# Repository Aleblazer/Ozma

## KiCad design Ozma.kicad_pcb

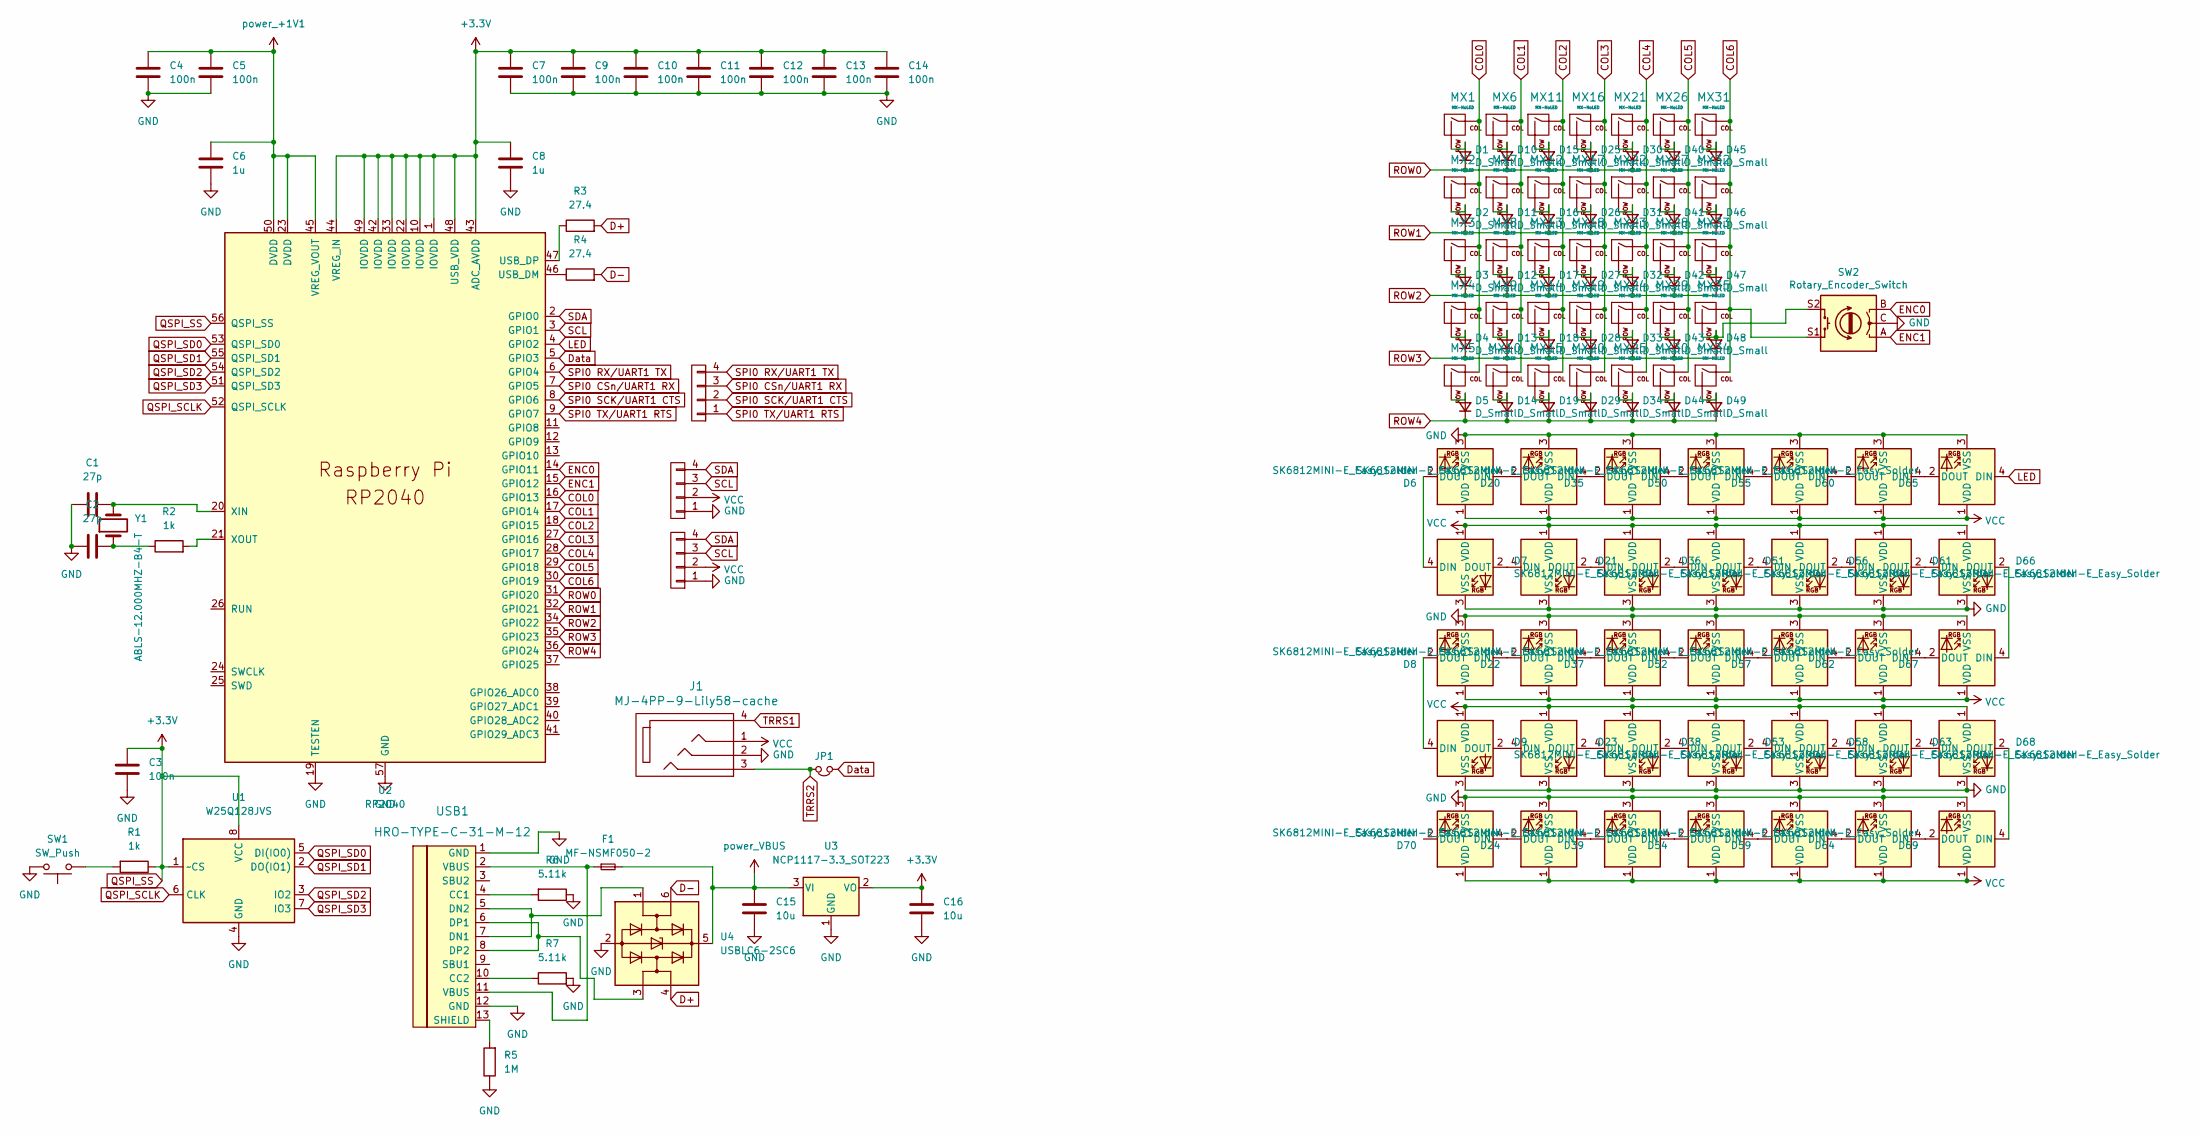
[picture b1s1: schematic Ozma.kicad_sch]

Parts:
C1, C2: 27p; R_0402_1005Metric; LCSC C1557
C3, C4, C5, C7, C9, C10, C11, C12, C13, C14: 100n; R_0402_1005Metric; LCSC C60474
C6, C8: 1u; R_0402_1005Metric; LCSC C314234
C15, C16: 10u; R_1206_3216Metric; LCSC C92790
D1, D2, D3, D4, D5, D10, D11, D12, D13, D14, D15, D16, D17, D18, D19, D25, D26, D27, D28, D29, D30, D31, D32, D33, D34, D40, D41, D42, D43, D44, D45, D46, D47, D48, D49: D_Small; D_SOD-123F; LCSC C132821
D6, D7, D8, D9, D20, D21, D22, D23, D24, D35, D36, D37, D38, D39, D50, D51, D52, D53, D54, D55, D56, D57, D58, D59, D60, D61, D62, D63, D64, D65, D66, D67, D68, D69, D70: SK6812MINI-E_Easy_Solder; YS-SK6812MINI-E
F1: MF-NSMF050-2; Fuse_1206_3216Metric; LCSC C75464
J1: MJ-4PP-9-Lily58-cache; MJ-4PP-9_rev2; LCSC C95562
JP1: Jumper_NC_Small; jumper_data
MX1, MX2, MX3, MX4, MX5, MX6, MX7, MX8, MX9, MX10, MX11, MX12, MX13, MX14, MX15, MX16, MX17, MX18, MX19, MX20, MX21, MX22, MX23, MX24, MX25, MX26, MX27, MX28, MX29, MX30, MX31, MX32, MX34, MX35: MX-NoLED; MX-Alps-Choc-1U-NoLED
MX33: MX-NoLED; MX-Alps-Choc-2u-StabFlip-NoLED
P1, P2, P3: OLED; OLED_4Pin
R1, R2: 1k; R_0402_1005Metric; LCSC C491161
R3, R4: 27.4; R_0402_1005Metric; LCSC C172043
R5: 1M; R_0402_1005Metric; LCSC C144054
R6, R7: 5.11k; R_0402_1005Metric; LCSC C25906
SW1: SW_Push; TACT_SWITCH_TVBP06
SW2: Rotary_Encoder_Switch; RotaryEncoder_EC11
U1: W25Q128JVS; SOIC-8_5.23x5.23mm_P1.27mm; LCSC C113767
U2: RP2040; RP2040-QFN-56; LCSC C2040
U3: NCP1117-3.3_SOT223; SOT-223-3_TabPin2; LCSC C233237
U4: USBLC6-2SC6; SOT-23-6; LCSC C2830148
USB1: HRO-TYPE-C-31-M-12; HRO-TYPE-C-31-M-12-Assembly; LCSC C165948
Y1: ABLS-12.000MHZ-B4-T; Crystal_SMD_HC49-US; LCSC C596818

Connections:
+1V1: C4.1, C5.1, C6.1, U2.23 (DVDD), U2.45 (VREG_VOUT), U2.50 (DVDD)
COL0: MX1.1 (COL), MX2.1 (COL), MX3.1 (COL), MX4.1 (COL), MX5.1 (COL), U2.16 (GPIO13)
COL1: MX6.1 (COL), MX7.1 (COL), MX8.1 (COL), MX9.1 (COL), MX10.1 (COL), U2.17 (GPIO14)
COL2: MX11.1 (COL), MX12.1 (COL), MX13.1 (COL), MX14.1 (COL), MX15.1 (COL), U2.18 (GPIO15)
COL3: MX16.1 (COL), MX17.1 (COL), MX18.1 (COL), MX19.1 (COL), MX20.1 (COL), U2.27 (GPIO16)
COL4: MX21.1 (COL), MX22.1 (COL), MX23.1 (COL), MX24.1 (COL), MX25.1 (COL), U2.28 (GPIO17)
COL5: MX26.1 (COL), MX27.1 (COL), MX28.1 (COL), MX29.1 (COL), MX30.1 (COL), U2.29 (GPIO18)
COL6: MX31.1 (COL), MX32.1 (COL), MX33.1 (COL), MX34.1 (COL), MX35.1 (COL), SW2.S1, U2.30 (GPIO19)
D+: R3.2, U4.4 (I/O2)
D-: R4.2, U4.6 (I/O1)
Data: JP1.1, U2.5 (GPIO3)
ENC0: SW2.B, U2.14 (GPIO11)
ENC1: SW2.A, U2.15 (GPIO12)
GND: C1.1, C2.1, C3.2, C4.2, C5.2, C6.2, C7.2, C8.2, C9.2, C10.2, C11.2, C12.2, C13.2, C14.2, C15.2, C16.2, D6.3 (VSS), D7.3 (VSS), D8.3 (VSS), D9.3 (VSS), D20.3 (VSS), D21.3 (VSS), D22.3 (VSS), D23.3 (VSS), D24.3 (VSS), D35.3 (VSS), D36.3 (VSS), D37.3 (VSS), D38.3 (VSS), D39.3 (VSS), D50.3 (VSS), D51.3 (VSS), D52.3 (VSS), D53.3 (VSS), D54.3 (VSS), D55.3 (VSS), D56.3 (VSS), D57.3 (VSS), D58.3 (VSS), D59.3 (VSS), D60.3 (VSS), D61.3 (VSS), D62.3 (VSS), D63.3 (VSS), D64.3 (VSS), D65.3 (VSS), D66.3 (VSS), D67.3 (VSS), D68.3 (VSS), D69.3 (VSS), D70.3 (VSS), J1.2, P1.1, P2.1, R5.1, R6.1, R7.2, SW1.2, SW2.C, U1.4 (GND), U2.19 (TESTEN), U2.57 (GND), U3.1 (GND), U4.2 (GND), USB1.1 (GND), USB1.12 (GND)
LED: D65.4 (DIN), U2.4 (GPIO2)
unnamed: C1.2, U2.20 (XIN), Y1.2
unnamed: C2.2, R2.1, Y1.1
unnamed: D1.2 (A), MX1.2 (ROW)
unnamed: D2.2 (A), MX2.2 (ROW)
unnamed: D3.2 (A), MX3.2 (ROW)
unnamed: D4.2 (A), MX4.2 (ROW)
unnamed: D5.2 (A), MX5.2 (ROW)
unnamed: D6.2 (DOUT), D7.4 (DIN)
unnamed: D8.2 (DOUT), D9.4 (DIN)
unnamed: D10.2 (A), MX6.2 (ROW)
unnamed: D11.2 (A), MX7.2 (ROW)
unnamed: D12.2 (A), MX8.2 (ROW)
unnamed: D13.2 (A), MX9.2 (ROW)
unnamed: D14.2 (A), MX10.2 (ROW)
unnamed: D15.2 (A), MX11.2 (ROW)
unnamed: D16.2 (A), MX12.2 (ROW)
unnamed: D17.2 (A), MX13.2 (ROW)
unnamed: D18.2 (A), MX14.2 (ROW)
unnamed: D19.2 (A), MX15.2 (ROW)
unnamed: D6.4 (DIN), D20.2 (DOUT)
unnamed: D20.4 (DIN), D35.2 (DOUT)
unnamed: D21.2 (DOUT), D36.4 (DIN)
unnamed: D7.2 (DOUT), D21.4 (DIN)
unnamed: D8.4 (DIN), D22.2 (DOUT)
unnamed: D22.4 (DIN), D37.2 (DOUT)
unnamed: D23.2 (DOUT), D38.4 (DIN)
unnamed: D9.2 (DOUT), D23.4 (DIN)
unnamed: D24.2 (DOUT), D70.4 (DIN)
unnamed: D24.4 (DIN), D39.2 (DOUT)
unnamed: D25.2 (A), MX16.2 (ROW)
unnamed: D26.2 (A), MX17.2 (ROW)
unnamed: D27.2 (A), MX18.2 (ROW)
unnamed: D28.2 (A), MX19.2 (ROW)
unnamed: D29.2 (A), MX20.2 (ROW)
unnamed: D30.2 (A), MX21.2 (ROW)
unnamed: D31.2 (A), MX22.2 (ROW)
unnamed: D32.2 (A), MX23.2 (ROW)
unnamed: D33.2 (A), MX24.2 (ROW)
unnamed: D34.2 (A), MX25.2 (ROW)
unnamed: D35.4 (DIN), D50.2 (DOUT)
unnamed: D36.2 (DOUT), D51.4 (DIN)
unnamed: D37.4 (DIN), D52.2 (DOUT)
unnamed: D38.2 (DOUT), D53.4 (DIN)
unnamed: D39.4 (DIN), D54.2 (DOUT)
unnamed: D40.2 (A), MX26.2 (ROW)
unnamed: D41.2 (A), MX27.2 (ROW)
unnamed: D42.2 (A), MX28.2 (ROW)
unnamed: D43.2 (A), MX29.2 (ROW)
unnamed: D44.2 (A), MX30.2 (ROW)
unnamed: D45.2 (A), MX31.2 (ROW)
unnamed: D46.2 (A), MX32.2 (ROW)
unnamed: D47.2 (A), MX33.2 (ROW)
unnamed: D49.2 (A), MX34.2 (ROW)
unnamed: D50.4 (DIN), D55.2 (DOUT)
unnamed: D51.2 (DOUT), D56.4 (DIN)
unnamed: D52.4 (DIN), D57.2 (DOUT)
unnamed: D53.2 (DOUT), D58.4 (DIN)
unnamed: D54.4 (DIN), D59.2 (DOUT)
unnamed: D55.4 (DIN), D60.2 (DOUT)
unnamed: D56.2 (DOUT), D61.4 (DIN)
unnamed: D57.4 (DIN), D62.2 (DOUT)
unnamed: D58.2 (DOUT), D63.4 (DIN)
unnamed: D59.4 (DIN), D64.2 (DOUT)
unnamed: D60.4 (DIN), D65.2 (DOUT)
unnamed: D61.2 (DOUT), D66.4 (DIN)
unnamed: D62.4 (DIN), D67.2 (DOUT)
unnamed: D63.2 (DOUT), D68.4 (DIN)
unnamed: D64.4 (DIN), D69.2 (DOUT)
unnamed: D66.2 (DOUT), D67.4 (DIN)
unnamed: D68.2 (DOUT), D69.4 (DIN)
unnamed: F1.1, USB1.2 (VBUS), USB1.11 (VBUS)
unnamed: R1.2, SW1.1
unnamed: R2.2, U2.21 (XOUT)
unnamed: R3.1, U2.47 (USB_DP)
unnamed: R4.1, U2.46 (USB_DM)
unnamed: R5.2, USB1.13 (SHIELD)
unnamed: R6.2, USB1.4 (CC1)
unnamed: R7.1, USB1.10 (CC2)
unnamed: D48.2 (A), MX35.2 (ROW), SW2.S2
unnamed: U4.1 (I/O1), USB1.5 (DN2), USB1.7 (DN1)
unnamed: U4.3 (I/O2), USB1.6 (DP1), USB1.8 (DP2)
QSPI_SCLK: U1.6 (CLK), U2.52 (QSPI_SCLK)
QSPI_SD0: U1.5 (DI(IO0)), U2.53 (QSPI_SD0)
QSPI_SD1: U1.2 (DO(IO1)), U2.55 (QSPI_SD1)
QSPI_SD2: U1.3 (IO2), U2.54 (QSPI_SD2)
QSPI_SD3: U1.7 (IO3), U2.51 (QSPI_SD3)
QSPI_SS: C3.1, C7.1, C8.1, C9.1, C10.1, C11.1, C12.1, C13.1, C14.1, C16.1, R1.1, U1.1 (~CS), U1.8 (VCC), U2.1 (IOVDD), U2.10 (IOVDD), U2.22 (IOVDD), U2.33 (IOVDD), U2.42 (IOVDD), U2.43 (ADC_AVDD), U2.44 (VREG_IN), U2.48 (USB_VDD), U2.49 (IOVDD), U2.56 (QSPI_SS), U3.2 (VO)
ROW0: D1.1 (K), D10.1 (K), D15.1 (K), D25.1 (K), D30.1 (K), D40.1 (K), D45.1 (K), U2.31 (GPIO20)
ROW1: D2.1 (K), D11.1 (K), D16.1 (K), D26.1 (K), D31.1 (K), D41.1 (K), D46.1 (K), U2.32 (GPIO21)
ROW2: D3.1 (K), D12.1 (K), D17.1 (K), D27.1 (K), D32.1 (K), D42.1 (K), D47.1 (K), U2.34 (GPIO22)
ROW3: D4.1 (K), D13.1 (K), D18.1 (K), D28.1 (K), D33.1 (K), D43.1 (K), D48.1 (K), U2.35 (GPIO23)
ROW4: D5.1 (K), D14.1 (K), D19.1 (K), D29.1 (K), D34.1 (K), D44.1 (K), D49.1 (K), U2.36 (GPIO24)
SCL: P1.3, P2.3, U2.3 (GPIO1)
SDA: P1.4, P2.4, U2.2 (GPIO0)
SPI0 CSn/UART1 RX: P3.3, U2.7 (GPIO5)
SPI0 RX/UART1 TX: P3.4, U2.6 (GPIO4)
SPI0 SCK/UART1 CTS: P3.2, U2.8 (GPIO6)
SPI0 TX/UART1 RTS: P3.1, U2.9 (GPIO7)
TRRS1: J1.4
TRRS2: J1.3, JP1.2
VBUS: C15.1, F1.2, U3.3 (VI), U4.5 (VBUS)
VCC: D6.1 (VDD), D7.1 (VDD), D8.1 (VDD), D9.1 (VDD), D20.1 (VDD), D21.1 (VDD), D22.1 (VDD), D23.1 (VDD), D24.1 (VDD), D35.1 (VDD), D36.1 (VDD), D37.1 (VDD), D38.1 (VDD), D39.1 (VDD), D50.1 (VDD), D51.1 (VDD), D52.1 (VDD), D53.1 (VDD), D54.1 (VDD), D55.1 (VDD), D56.1 (VDD), D57.1 (VDD), D58.1 (VDD), D59.1 (VDD), D60.1 (VDD), D61.1 (VDD), D62.1 (VDD), D63.1 (VDD), D64.1 (VDD), D65.1 (VDD), D66.1 (VDD), D67.1 (VDD), D68.1 (VDD), D69.1 (VDD), D70.1 (VDD), J1.1, P1.2, P2.2

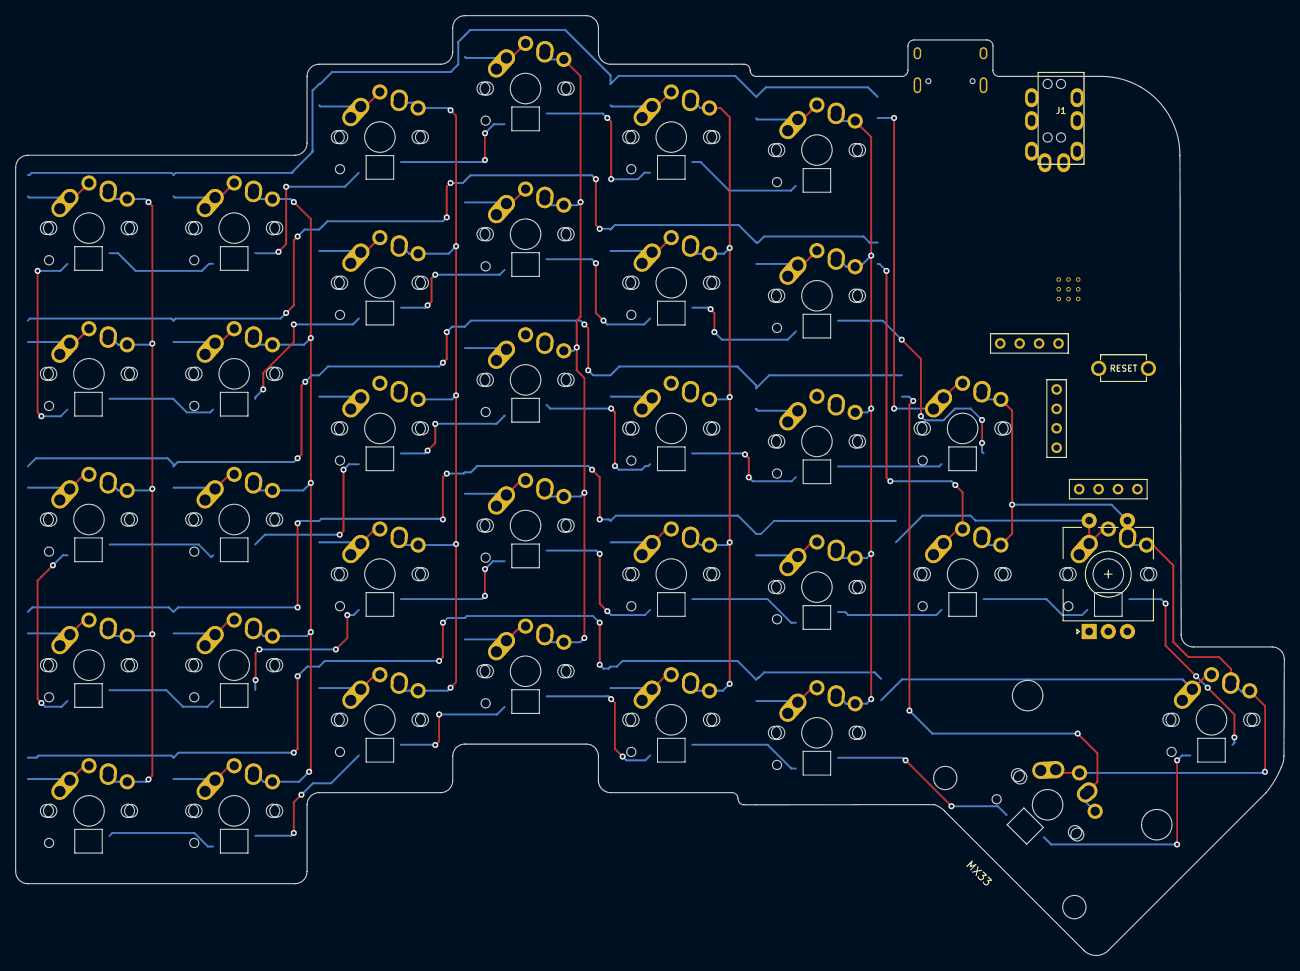
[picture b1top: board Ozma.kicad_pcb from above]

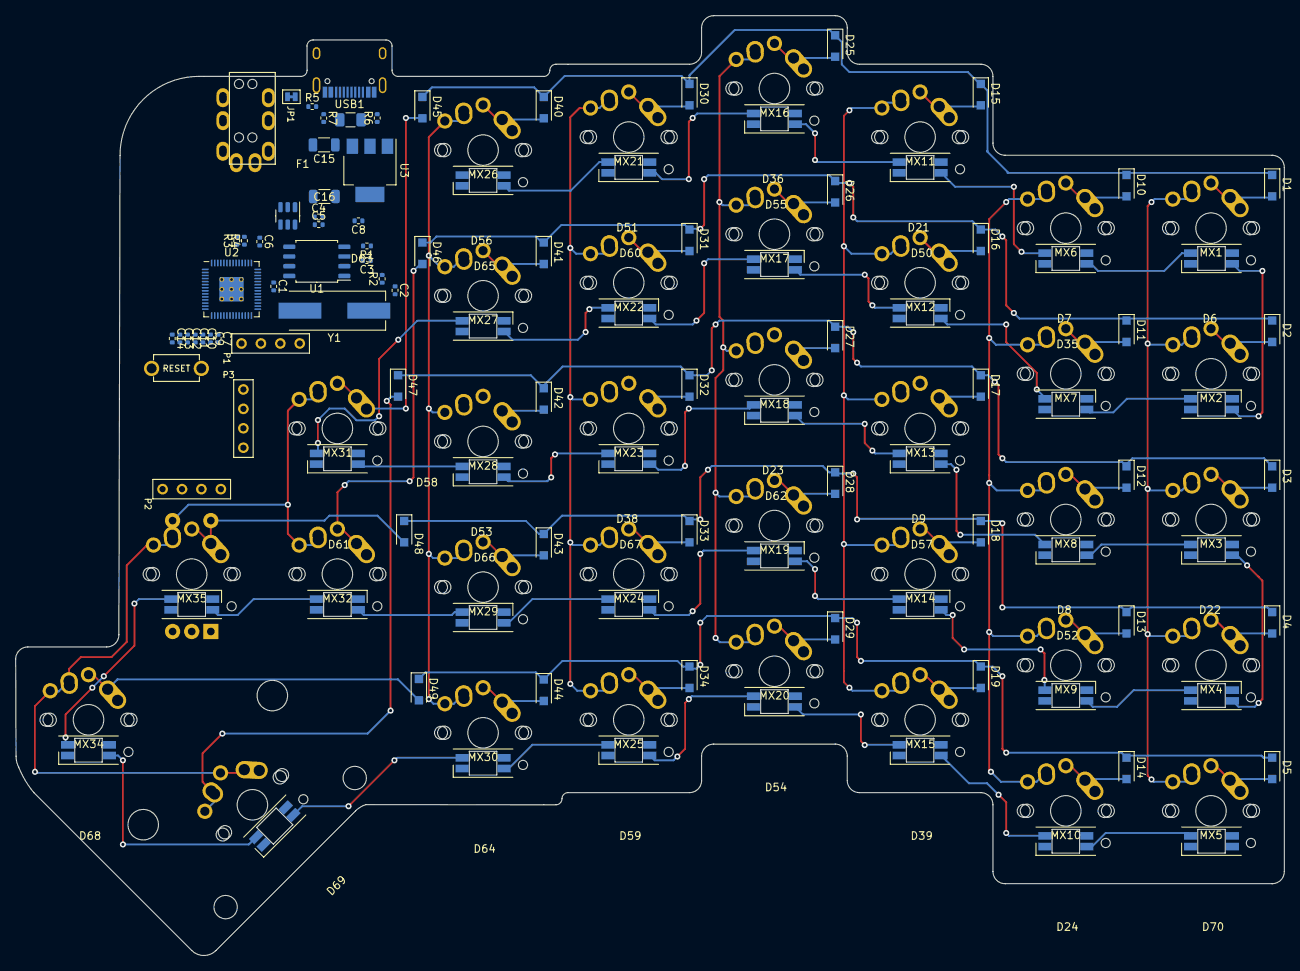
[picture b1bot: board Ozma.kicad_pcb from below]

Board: 2 copper layers, 165.9 x 122.9 mm, 142 parts (105 on the bottom side), 116 nets.

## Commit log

2021-07-11 Trace Work Started
2021-07-11 Design updates
2021-07-20 Sync
